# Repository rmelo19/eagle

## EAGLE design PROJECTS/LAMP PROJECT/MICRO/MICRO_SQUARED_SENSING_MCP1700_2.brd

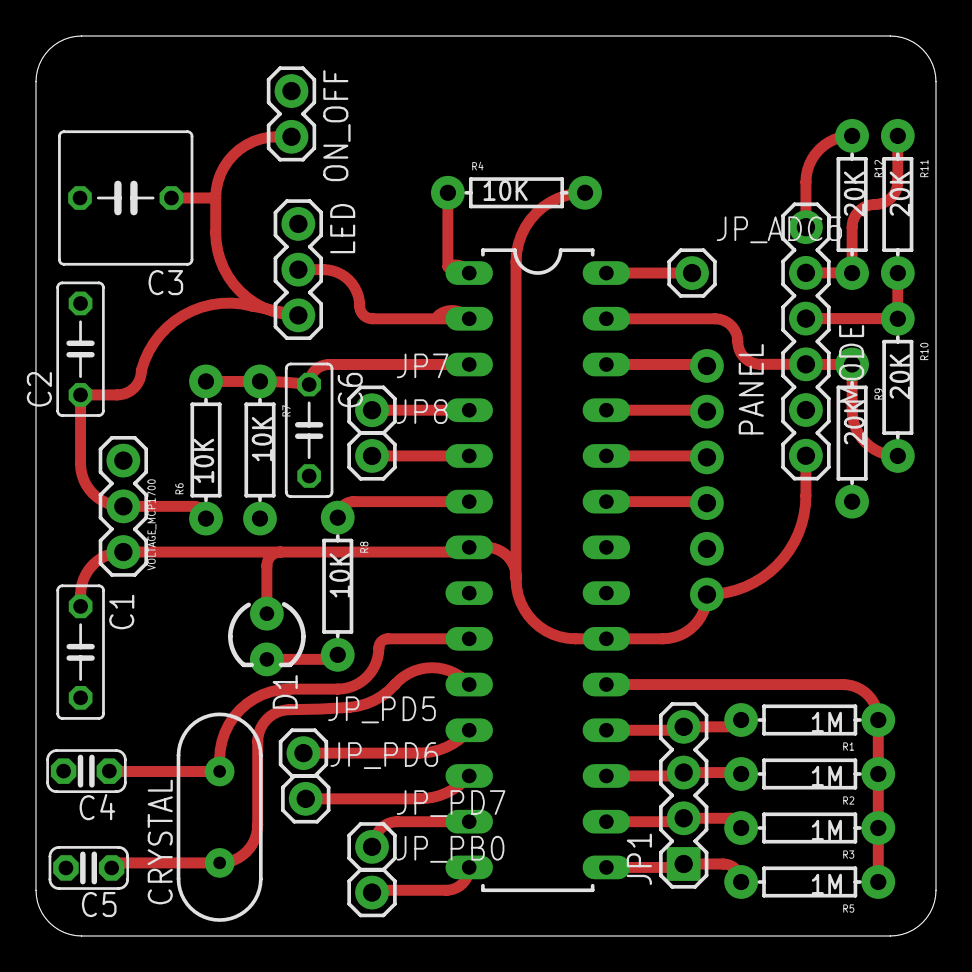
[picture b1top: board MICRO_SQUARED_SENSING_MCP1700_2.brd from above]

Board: 2 copper layers, 50.0 x 50.0 mm, 34 parts (0 on the bottom side), 30 nets.

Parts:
BRAIN: ATMEGA328P_PDIP; DIL-28-3
C1, C2, C6: 1u; C050-025X075
C3: 1000uF; C050-075X075
C4, C5: 22pF; C025-024X044
CRYSTAL: HC49US
D1: LED3MM
JP1: 1X04
JP7, JP8: 1X01
JP_ADC5: 1X01
JP_PB0: 1X01
JP_PD5, JP_PD6, JP_PD7: 1X01
LED: 1X03
MODE: 1X06
ON_OFF: 1X02
PANEL: 1X06_NO_SILK
R1, R2, R3, R5: 1M; AXIAL-0.3
R4, R6, R7, R8: 10K; AXIAL-0.3
R9, R10, R11, R12: 20K; AXIAL-0.3
VOLTAGE_MCP1700: 1X03

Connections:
BLUE_BRAIN: BRAIN.25, PANEL.2
GND: BRAIN.8, BRAIN.22, C1.2, C2.2, C3.2, C4.2, C5.2, C6.2, LED.1, MODE.2, ON_OFF.1, PANEL.5, R7.P$2, R9.P$2, VOLTAGE_MCP1700.3
GREEN_BRAIN: BRAIN.24, PANEL.3
LEDS_BRAIN: BRAIN.2, LED.2
unnamed: BRAIN.3, C6.1, R6.P$2, R7.P$1
unnamed: BRAIN.15, JP1.1, R5.P$2
unnamed: BRAIN.16, JP1.2, R3.P$2
unnamed: BRAIN.17, JP1.3, R2.P$2
unnamed: BRAIN.18, JP1.4, R1.P$2
unnamed: BRAIN.19, R1.P$1, R2.P$1, R3.P$1, R5.P$1
unnamed: BRAIN.9, C4.1, CRYSTAL.2
unnamed: BRAIN.10, C5.1, CRYSTAL.1
unnamed: BRAIN.5, JP8.1
unnamed: D1.K, R8.P$2
unnamed: BRAIN.6, R8.P$1
unnamed: BRAIN.4, JP7.1
unnamed: BRAIN.27, MODE.3, R9.P$1, R10.P$2
unnamed: BRAIN.12, JP_PD6.1
unnamed: BRAIN.13, JP_PD7.1
unnamed: BRAIN.14, JP_PB0.1
unnamed: BRAIN.28, JP_ADC5.1
unnamed: BRAIN.11, JP_PD5.1
unnamed: MODE.6, R12.P$1
unnamed: MODE.5, R11.P$1, R12.P$2
unnamed: MODE.4, R10.P$1, R11.P$2
RED_BRAIN: BRAIN.26, PANEL.1
RST: BRAIN.1, R4.P$1
SPEED_BRAIN: BRAIN.23, PANEL.4
SWITCH_BRAIN: C2.1, C3.1, LED.3, ON_OFF.2, R6.P$1, VOLTAGE_MCP1700.2
V_5V: BRAIN.7, BRAIN.20, C1.1, D1.A, MODE.1, PANEL.6, R4.P$2, VOLTAGE_MCP1700.1

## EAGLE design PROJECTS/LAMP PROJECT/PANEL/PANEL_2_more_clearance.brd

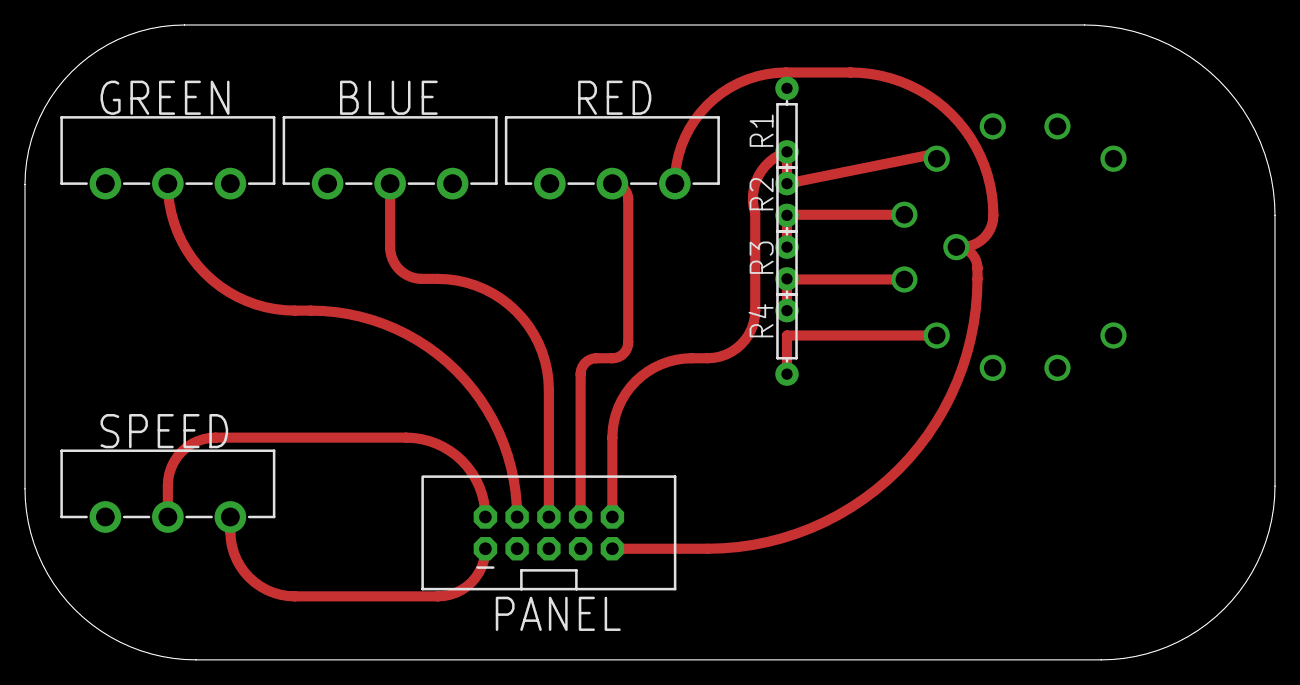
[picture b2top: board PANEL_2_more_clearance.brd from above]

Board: 2 copper layers, 100.0 x 50.8 mm, 10 parts (0 on the bottom side), 10 nets.

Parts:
BLUE: POT_ALPHA_RV16AF-20
CHANGE_MODE: 1x10; ROTARY_SWITCH_1X10
GREEN: POT_ALPHA_RV16AF-20
PANEL: 2X5-SHROUDED
R1, R2, R3, R4: 20K; AXIAL-0.3EZ
RED: POT_ALPHA_RV16AF-20
SPEED: POT_ALPHA_RV16AF-20

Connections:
GND: BLUE.1, GREEN.1, PANEL.5, R1.P$2, RED.1, SPEED.1
unnamed: CHANGE_MODE.4, R4.P$1
unnamed: CHANGE_MODE.5, R3.P$1, R4.P$2
unnamed: CHANGE_MODE.6, R2.P$1, R3.P$2
PANEL_BLUE: BLUE.2, PANEL.6
PANEL_GREEN: GREEN.2, PANEL.4
PANEL_MODE: CHANGE_MODE.7, PANEL.10, R1.P$1, R2.P$2
PANEL_RED: PANEL.8, RED.2
PANEL_SPEED: PANEL.2, SPEED.2
PANEL_V_5V: BLUE.3, CHANGE_MODE.COMMON, GREEN.3, PANEL.1, PANEL.9, RED.3, SPEED.3

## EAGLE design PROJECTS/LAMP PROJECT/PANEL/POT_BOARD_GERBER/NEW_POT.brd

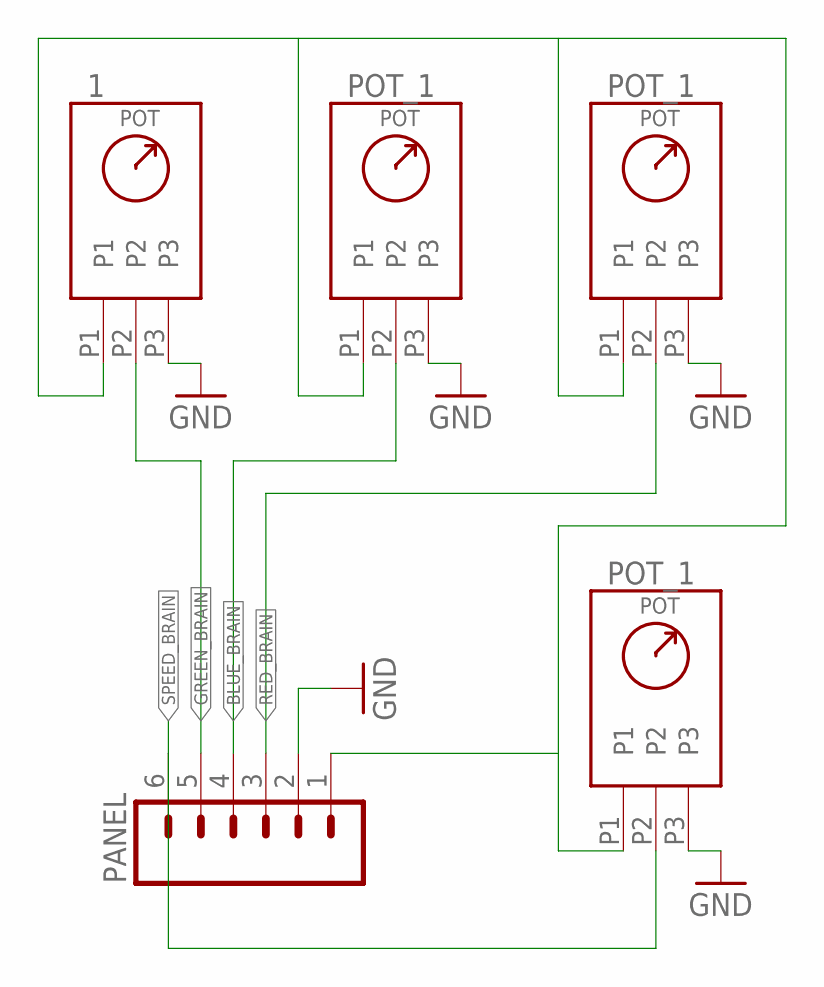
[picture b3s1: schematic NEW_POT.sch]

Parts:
DAS: 1; POT_1
PANEL: M06NO_SILK_FEMALE_PTH; 1X06_NO_SILK
U$2, U$3, U$4: POT_1

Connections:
BLUE_BRAIN: PANEL.4, U$2.P2
GND: DAS.P3, PANEL.2, U$2.P3, U$3.P3, U$4.P3
GREEN_BRAIN: DAS.P2, PANEL.5
RED_BRAIN: PANEL.3, U$3.P2
SPEED_BRAIN: PANEL.6, U$4.P2
V_5V: DAS.P1, PANEL.1, U$2.P1, U$3.P1, U$4.P1

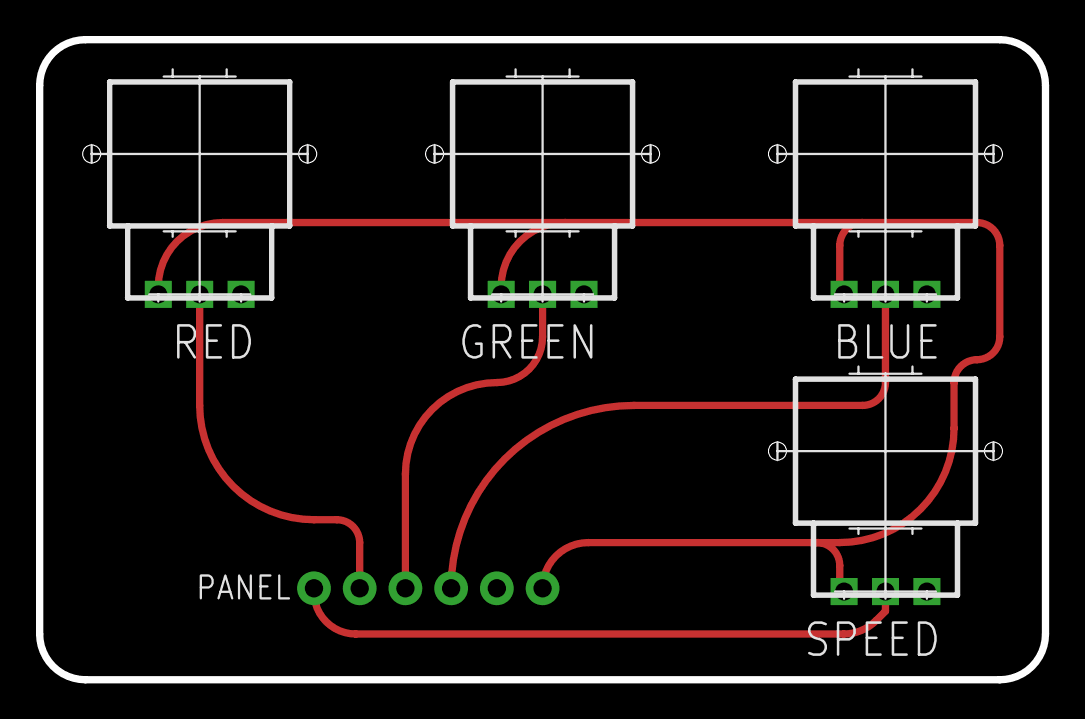
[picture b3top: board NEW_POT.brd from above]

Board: 2 copper layers, 55.9 x 35.6 mm, 5 parts (0 on the bottom side), 6 nets.

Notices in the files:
parts and their libraries:
SparkFun-FreqCtrl: Licensing: Creative Commons ShareAlike 4.0 International - https://creativecommons.org/licenses/by-sa/4.0
